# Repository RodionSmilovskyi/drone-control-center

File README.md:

# Useful commands
ssh rodion@10.0.0.131  
scp server.py  rodion@10.0.0.131:~/drone  

# Sample GUI output
Press 'q' to quit, 'r' to reboot, 'm' to change mode, 'a' to arm, 'd' to disarm and arrow keys to control  

ARMED: False                                      armingDisableFlags: []
cpuload: 23                                       cycleTime: 248
mode: 0                                           Flight Mode: []
Battery Voltage: 16.02V VOLTAGE TOO HIGH
Motor Values: [1000, 1000, 1000, 1000, 0, 0, 0, 0]
Attitude: [-1.3, -1.3, 73]
Altitude: 3.04
RC Channels Values: [1500, 1500, 1500, 900, 1000, 1000, 1500, 1500, 1500, 1500, 1500, 1500, 1500, 1500, 1500, 1500, 1500GUI cycleTime: 15.99ms (average 62.54Hz)]

apiVersion: 1.46.0                                flightControllerIdentifier: BTFL
flightControllerVersion: 4.5.2                    boardIdentifier: S405
boardName: SPEEDYBEEF405MINI                      name:

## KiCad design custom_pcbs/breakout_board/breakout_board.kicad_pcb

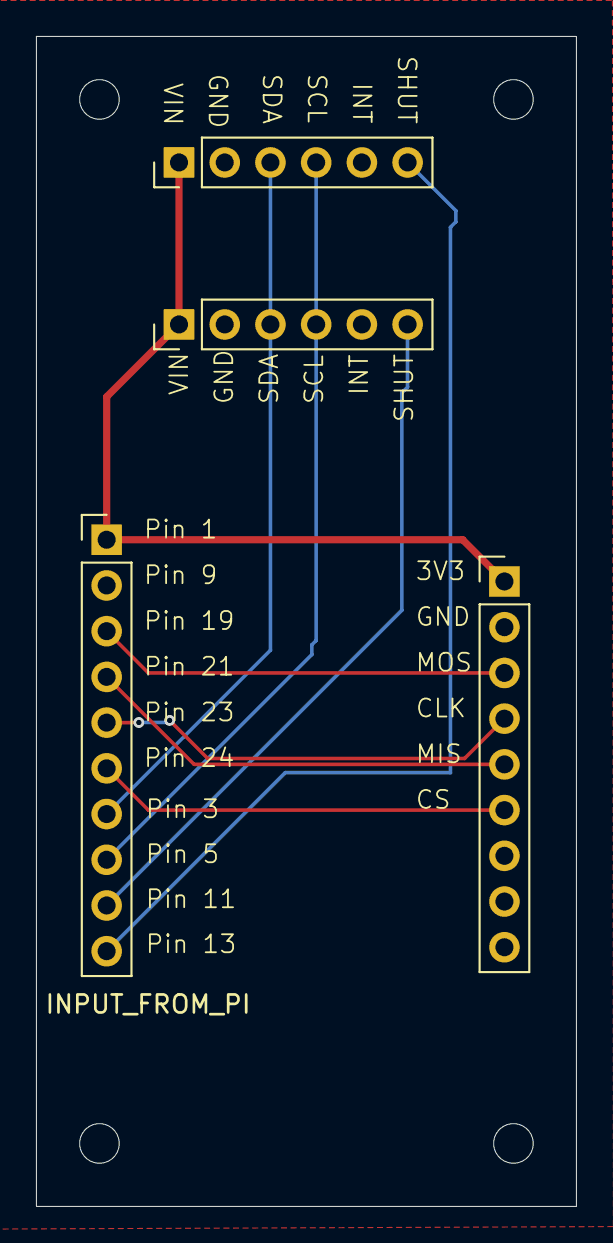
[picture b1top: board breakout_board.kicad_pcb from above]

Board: 4 copper layers, 30.0 x 65.0 mm, 8 parts (0 on the bottom side), 10 nets.

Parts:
H1, H2, H3, H4: MountingHole; MountingHole_2.2mm_M2
J1: INPUT_FROM_PI; PinHeader_1x10_P2.54mm_Vertical
J2: PMW3901_OUT; PinHeader_1x09_P2.54mm_Vertical
VL53L1X_1_OUT, VL53L1X_2_OUT: Conn_01x06; PinHeader_1x06_P2.54mm_Vertical

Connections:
+3V3: J1.1, J2.1, VL53L1X_1_OUT.1, VL53L1X_2_OUT.1
/I2C_SCL: J1.8, VL53L1X_1_OUT.4, VL53L1X_2_OUT.4
/I2C_SDA: J1.7, VL53L1X_1_OUT.3, VL53L1X_2_OUT.3
/SPI_CLK: J1.5, J2.4
/SPI_CS: J1.6, J2.6
/SPI_MISO: J1.4, J2.5
/SPI_MOSI: J1.3, J2.3
/XSHUT_1: J1.9, VL53L1X_1_OUT.6
/XSHUT_2: J1.10, VL53L1X_2_OUT.6
GND: J1.2, J2.2, VL53L1X_1_OUT.2, VL53L1X_2_OUT.2

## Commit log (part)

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2025-07-12 Added vscode settings and project requirments
2025-07-12 Added basic UI client for debugging
2025-07-12 Added sample of client server design
2025-09-14 Updated versions of client and simpleUi
2025-09-14 collecting debug info
2025-09-14 Added new dependecies and onnx model
2025-09-15 Updated gitignore to exclude pyenv version
2025-09-15 Swithed to tflite inference
2025-09-15 added drone calibration
2025-09-15 Added minimalitsitc client and started to plug AI
2025-10-26 Added mqtt lib
2025-10-26 added drone dashboard
2025-10-29 Updated tmux launch and mqtt interface
2025-10-29 Updated real drone controller
2025-10-31 House keeping
2025-11-01 Added loging
2025-11-01 fixed simple ui
2025-11-02 Working fc interface
2025-11-03 Added AI control, needs debug
2025-11-03 added more logging
2025-11-24 updated sensor check
2025-11-25 Added new sensors support
2025-11-25 Fixed launch script
2025-11-25 Fixed sensor logic
2025-11-25 Minor logging erro fix and temporary disabled commands
2026-02-08 Added 3d printed parts
2026-02-08 removed unused parts
2026-02-09 Updated design
2026-04-17 Added assembly for drone cage
2026-04-17 Updates from device
2026-04-17 Made flight controller consistent with training setup
2026-04-17 Adjusting observation
2026-04-17 Added test scripts
2026-04-17 Added sensor test script
2026-04-17 Added logging
2026-04-17 NEw sensor check scrpt
2026-04-17 Updated flow scalar
2026-04-17 FLow scalar 0.18
2026-04-17 flow scalar 0,45
2026-04-17 Added agent reset
2026-04-17 Flow scalar update back to 0.08
2026-04-17 flow coef set to 0.14
2026-04-17 Live policy testing
2026-04-17 Updated test policy script
2026-04-17 Updated test_policy_launcher setup
2026-04-18 Updated drone logging
2026-04-18 Updated policy logger
2026-04-18 Updated tactical controller
2026-04-18 One more log update
2026-04-18 Separate topic for logging
2026-04-18 Fixed path issue
2026-04-18 Removed stalle process
2026-04-18 Updated launchert
2026-04-18 Updated strategic agent
2026-04-18 Added missing except block
2026-04-18 Added missing import
2026-04-18 MOre robust logging
2026-04-18 More fixes
2026-04-18 Added heartbeat
2026-04-18 Chnaged format
2026-04-18 Fixed launcher
2026-04-18 Morfe updates
2026-04-18 Simplified log
2026-04-18 test policy update
2026-04-18 More fixe
2026-04-18 Send armed often
2026-04-18 Fix json errors
2026-04-18 Fix data leak
2026-04-18 Fixed comment error
2026-04-18 Pip tools integration
2026-04-18 Added GEMINI.md file for project context and instructions
2026-04-18 Added shared memory manager and tests
2026-04-18 Dasboard with dummy text
2026-04-19 Moved to service based architecture
2026-04-19 Updated real sensor
2026-04-19 Fixed drone service for pi
2026-04-19 Updated real sensor output
2026-04-19 Sensor fix
2026-04-19 Updated drone service to point to pyenv python
2026-04-19 Updated requirements
2026-04-19 Sensor and depenmdency fix
2026-04-19 Updated sensor indent fix
2026-04-19 Moved sensor to separate thread
2026-04-19 horizontal sensor shift fix
2026-04-19 Sensor update
2026-04-19 Keep debugging sensors
2026-04-19 Added debug log
2026-04-19 Lowered auto reset theshold
2026-04-19 CHnaged sensor coef
2026-04-19 Removed deadbandf but added lock
2026-04-19 More sensor fixes
2026-04-19 Added smoothing
2026-04-19 Reverted flow scalar
2026-04-19 flow scalar 1.14
2026-04-19 Sensor calibration
2026-04-20 Continue calibration
2026-04-20 Scalar flow 0.3
2026-04-20 More updated of flow
2026-04-20 More calibration
2026-04-20 flow ratio 0.94
2026-04-20 Debuggin info
2026-04-20 More debugging
2026-04-20 Added warmup
2026-04-20 Back to flow 0.34
2026-04-20 More adjustments
2026-04-20 Another calibration adjustment
2026-04-20 Flow 0.152
2026-04-20 Adjust movement
2026-04-20 More smooothing
2026-04-20 Back to 0.565
2026-04-20 Optical flow refacotring
2026-04-20 More deadband updates
2026-04-20 FLow updates
2026-04-20 new sensor check
2026-04-20 cumulative sensor check
2026-04-23 Updated sensor after lense installation
2026-04-23 Updated sensor rotation
2026-04-23 Updated directions
2026-04-26 Created dedicated shared memory for heartbeat
2026-04-26 Added dashboard mode handling
2026-04-26 Basic working version of drone-inference service
2026-04-26 Updated dashboard panels
2026-04-27 Provided a way to silence logging
2026-04-28 Implemented basic logic to hover at the altitude 0.3
2026-04-29 Updated gemini requirements
2026-04-29 Fixed dashboard rc_command order issue
2026-04-29 Removed unused dependencies
2026-04-29 Hardcoded altitude to 0.3
2026-04-29 Dynamic time loop
2026-04-30 Basic version of flight controller
2026-05-01 Add fc health status
2026-05-01 Fixed heartbeat issue
2026-05-01 Fixed opening port error
2026-05-01 Fixed arming issue
2026-05-01 increased max throttle
2026-05-01 Increaded max throttle to 1550
2026-05-01 Increased max throttle to 1600
2026-05-02 trying dynamic timestamp
2026-05-02 Increased hovee htottle to 1550
2026-05-02 Increased max throttle to 1800
2026-05-02 flight controll tuning, kd=0.5
2026-05-02 Inference fix
2026-05-02 Kp=3, Ki=0, Kd=0.1
2026-05-02 Intorudced integral limit
2026-05-02 Smoothed setpoints
2026-05-03 Adjusted bottom stands
2026-05-16 Updated gemini.md
2026-05-16 Added log cleanup
2026-05-16 Log handling update
2026-05-16 Updated infernce service definition
2026-05-16 Updated setpoint to 0.4
2026-06-07 Working on module enclosure
2026-06-08 Almost done, only video and power cable left
2026-06-08 Added video opening
2026-06-08 Added grill
2026-06-09 Redesigned power inlet to xh-2a
2026-06-09 Added engraving
2026-06-11 Exported printed parts
2026-06-11 Increased usb opening
2026-06-11 Modified engraving
2026-06-11 Modified cooling grill
2026-06-12 Started to work on breakout board design
2026-06-12 Basic pcb version
2026-06-12 Added more sensors
